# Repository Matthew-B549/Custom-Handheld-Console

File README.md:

# Custom-Handheld-Console
This repo is a collection of the hardware and software which make-up my Custom Handheld Console. You can find my PCB files here. I have also documented my thoughts and improvements that could be made to the project.

I have created a helpful pixel editor tool for creating artwork to display on the console. This tool can be found here: https://github.com/Matthew-B549/PixelEditor

**My inspiration**:
This project was largely inspired by the Nintendo Game Boy. In contrast to the cartridge style, all of the software is installed directly onto the ESP32. The software that I have uploaded includes 15 games (my favorite one being pong), but you are able to code in more of your own. The SD card (visible in the pictures at the bottom) is used to store high scores, but it can be repurposed in the software.

**Agentic Coding**:
In this project, I experimented with Agentic coding. I found that the various Agents that I used were able to iterate incredibly quickly to varying levels of results. Individually, many of the games are decently coded and perform well. However, I found that the Agents struggled in creating a unified system and some of the code is messy at times.

**What Changed V1 to V2?**
The primary change from V1 to V2 was in size. I shrunk the PCB from 133mm by 170mm to 100mm by 100mm. (*Note: I have no Idea how I chose the dimensions 133 by 170 originally, but the board went from being comically large to a more standard size*) This dramatic decrease in size led to more intentional routing being necessary. I completely remapped the ESP32 pins from V1 to V2 to optimize and reduce vias and crossing traces. I also focused on signal integrity by placing resistors along high frequency SPI communication lines. Additionally, I routed the speaker signal trace intentionally to try and minimize noise and crosstalk.

**What Changed V2 to V3?**
The only thing changed from V2 to V3 is the ESP32 footprint. In my first two versions, the PCB footprint was much smaller than my microcontroller's footprint. I had to bend the pins to make it fit in. This is mainly because of errors I made in measuring and using other models I had found online. To ensure that the V3 footprint is correct, I first made a CAD model of my ESP32 in Fusion. I then 3d printed it and made sure it was the exact same size. I then made the footprint with the same specifications from CAD and ensured that the CAD model and the footprint fit together.

**My Reflection**
This was my first project in which I made a PCB and I am exceptionally proud with the results. While there was much improvement from V1 to V2, there are still some issues I have come across when testing and using the Handheld Console. I have outlined some of the issues below:

* The ESP32 sometimes struggles to boot. This issue is likely due to weak battery connections and loosely attached power system on the back. On the back of the PCB, the battery, the buck boost converter, and the charging module are taped to the PCB. The PCB was not designed with this power system in mind. (In a similar fashion, the speaker is also taped to the back).

* I have not made a 3d printed case for this project. This is largely because of the irregular shape of the components mounted on the PCB. Large capacitors (among other components) poke through where the case would be. Again, the PCB was not designed specifically to work with a 3d printed case. These are all considerations that should be made earlier on in the process before ordering the PCB to ensure that both parts of the equation fit together.

* Even through my first 2 revisions and many measurements, the footprint for the ESP32 is slightly too small and pins may need to be bent in order to fit the footprint and be soldered in. ***This is fixed in V3***

* These design flaws heavily impact my experience when using the Console. They also make the Console very fragile and difficult to pass around and share.

I have included various pictures of the process and end result below.

Here is some of my earliest prototyping:
-----

Then I designed V1:
-----

V1 was way to big and had various flaws. Here is *a less flawed* V2:
-----

Notice the usage of tape:
-----

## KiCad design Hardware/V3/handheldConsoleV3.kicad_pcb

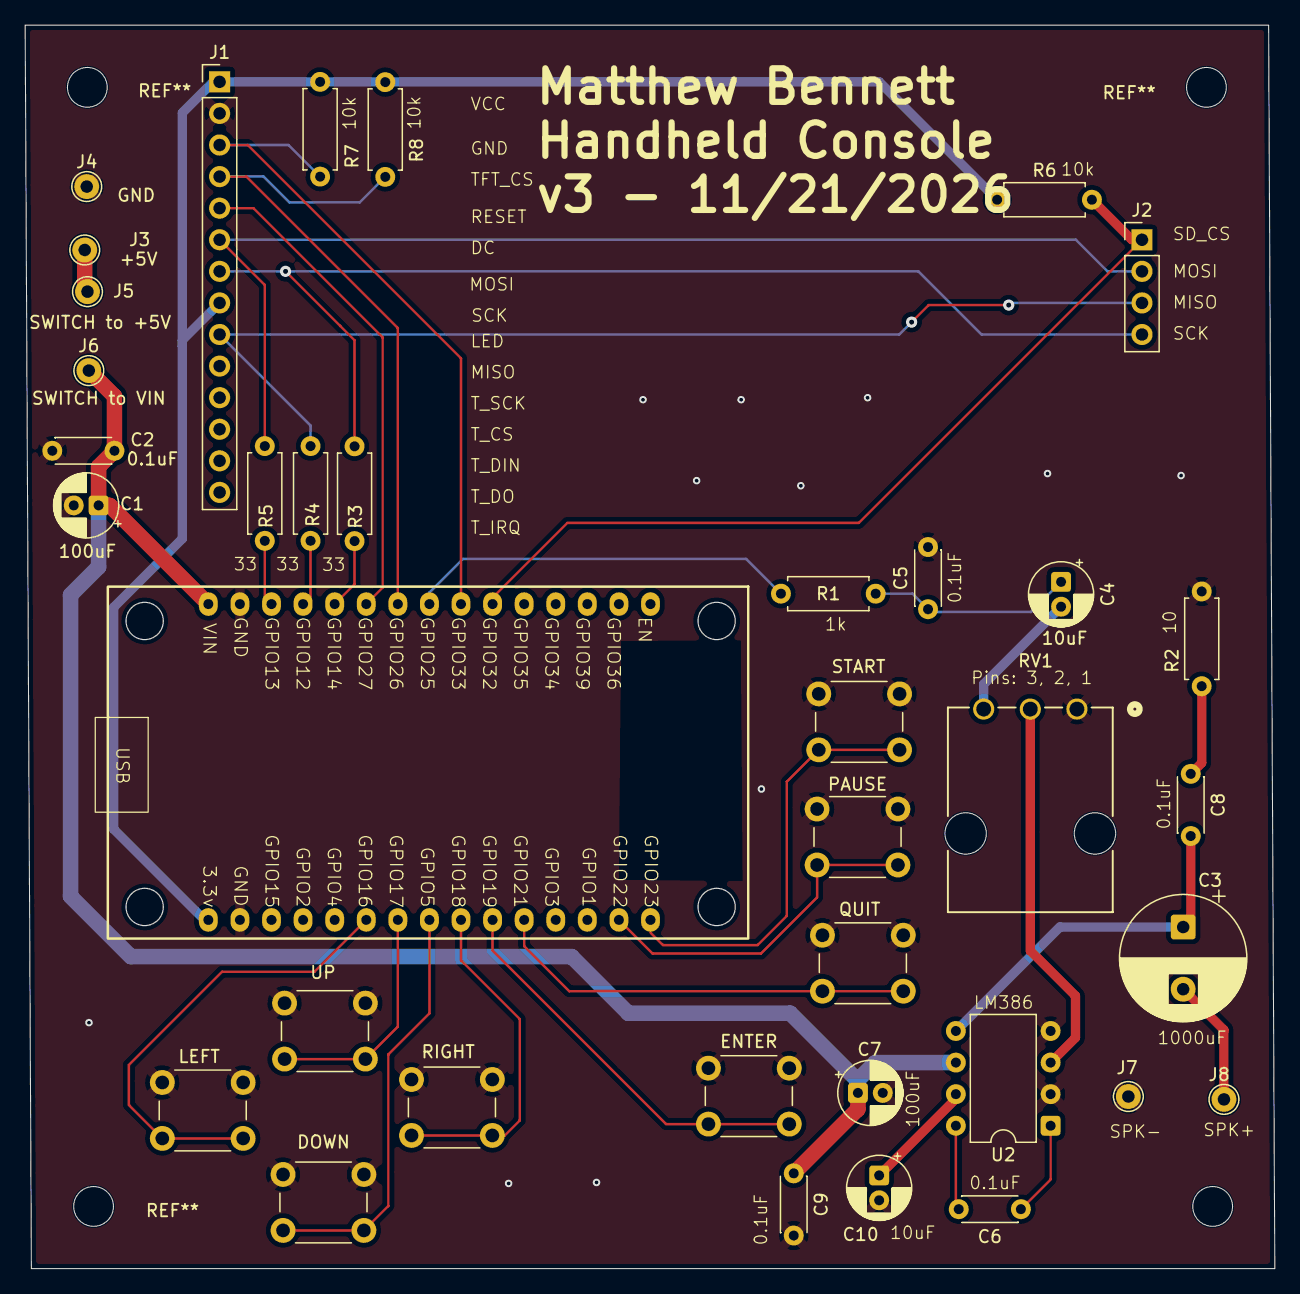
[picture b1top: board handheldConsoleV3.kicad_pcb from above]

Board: 2 copper layers, 100.5 x 100.0 mm, 37 parts (0 on the bottom side), 32 nets.

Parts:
C1, C7: 100uF; CP_Radial_D5.0mm_P2.00mm
C2, C5, C6, C8, C9: 0.1uF; C_Disc_D4.3mm_W1.9mm_P5.00mm
C3: 1000uF; CP_Radial_D10.0mm_P5.00mm
C4, C10: 10uF; CP_Radial_D5.0mm_P2.00mm
DOWN: SW_Push; SW_PUSH_6mm_H4.3mm
ENTER: SW_Push; SW_PUSH_6mm_H4.3mm
J1: Screen_Pins; PinHeader_1x14_P2.54mm_Vertical
J2: SD_Pins; PinHeader_1x04_P2.54mm_Vertical
J3, J4, J5, J6, J7, J8: Conn_01x01; TestPoint_THTPad_D2.0mm_Drill1.0mm
LEFT: SW_Push; SW_PUSH_6mm_H4.3mm
PAUSE: SW_Push; SW_PUSH_6mm_H4.3mm
QUIT: SW_Push; SW_PUSH_6mm_H4.3mm
R1: 1k; R_Axial_DIN0207_L6.3mm_D2.5mm_P7.62mm_Horizontal
R2: 10; R_Axial_DIN0207_L6.3mm_D2.5mm_P7.62mm_Horizontal
R3, R4, R5: 33; R_Axial_DIN0207_L6.3mm_D2.5mm_P7.62mm_Horizontal
R6, R7, R8: 10k; R_Axial_DIN0207_L6.3mm_D2.5mm_P7.62mm_Horizontal
RIGHT: SW_Push; SW_PUSH_6mm_H4.3mm
RV1: R_Potentiometer; POT_P120PK-x25_TTE
START: SW_Push; SW_PUSH_6mm_H4.3mm
U1: ESP32_30pin
U2: LM386; DIP-8_W7.62mm
UP: SW_Push; SW_PUSH_6mm_H4.3mm

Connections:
+3V3: J1.1, J1.8, R6.1, R7.1, R8.1, U1.16 (3.3v)
+5V: C1.1, C2.1, C7.1, C9.1, J6.1 (Pin_1_1), U1.1 (VIN), U2.6 (V+)
/DAC_AUDIO: R1.1, U1.8 (GPIO25)
/DC: J1.5, U1.6 (GPIO27)
/DOWN_BTN: DOWN.2, U1.23 (GPIO5)
/ENTER_BTN: ENTER.2, U1.25 (GPIO19)
/LEFT_BTN: LEFT.2, U1.21 (GPIO16)
/MISO: J1.9, J2.3, R4.2
/MOSI: J1.6, J2.2, R5.2
/PAUSE_BTN: START.2, U1.30 (GPIO23)
/QUIT_BTN: PAUSE.2, U1.29 (GPIO22)
/RESET: J1.4, R8.2, U1.7 (GPIO26)
/RIGHT_BTN: RIGHT.2, U1.24 (GPIO18)
/SCK: J1.7, J2.4, R3.2
/SD_CS: J2.1, R6.2, U1.10 (GPIO32)
/START_BTN: QUIT.2, U1.26 (GPIO21)
/TFT_CS: J1.3, R7.2, U1.9 (GPIO33)
/UP_BTN: U1.22 (GPIO17), UP.2
GND: C1.2, C2.2, C5.2, C7.2, C9.2, C10.2, DOWN.1, ENTER.1, J1.2, J4.1 (Pin_1_1), J7.1 (Pin_1_1), LEFT.1, PAUSE.1, QUIT.1, R2.1, RIGHT.1, RV1.1, START.1, U1.2 (GND), U1.17 (GND), U2.2 (-), U2.4 (GND), UP.1
unnamed: C3.1, C8.2, U2.5
unnamed: C4.1, C5.1, R1.2
unnamed: C4.2, RV1.3
unnamed: C6.1, U2.1 (GAIN)
unnamed: C6.2, U2.8 (GAIN)
unnamed: C8.1, R2.2
unnamed: J3.1 (Pin_1_1), J5.1 (Pin_1_1)
unnamed: C3.2, J8.1 (Pin_1_1)
unnamed: R4.1, U1.4 (GPIO12)
unnamed: R5.1, U1.3 (GPIO13)
unnamed: R3.1, U1.5 (GPIO14)
unnamed: RV1.2, U2.3 (+)
unnamed: C10.1, U2.7 (BYPASS)

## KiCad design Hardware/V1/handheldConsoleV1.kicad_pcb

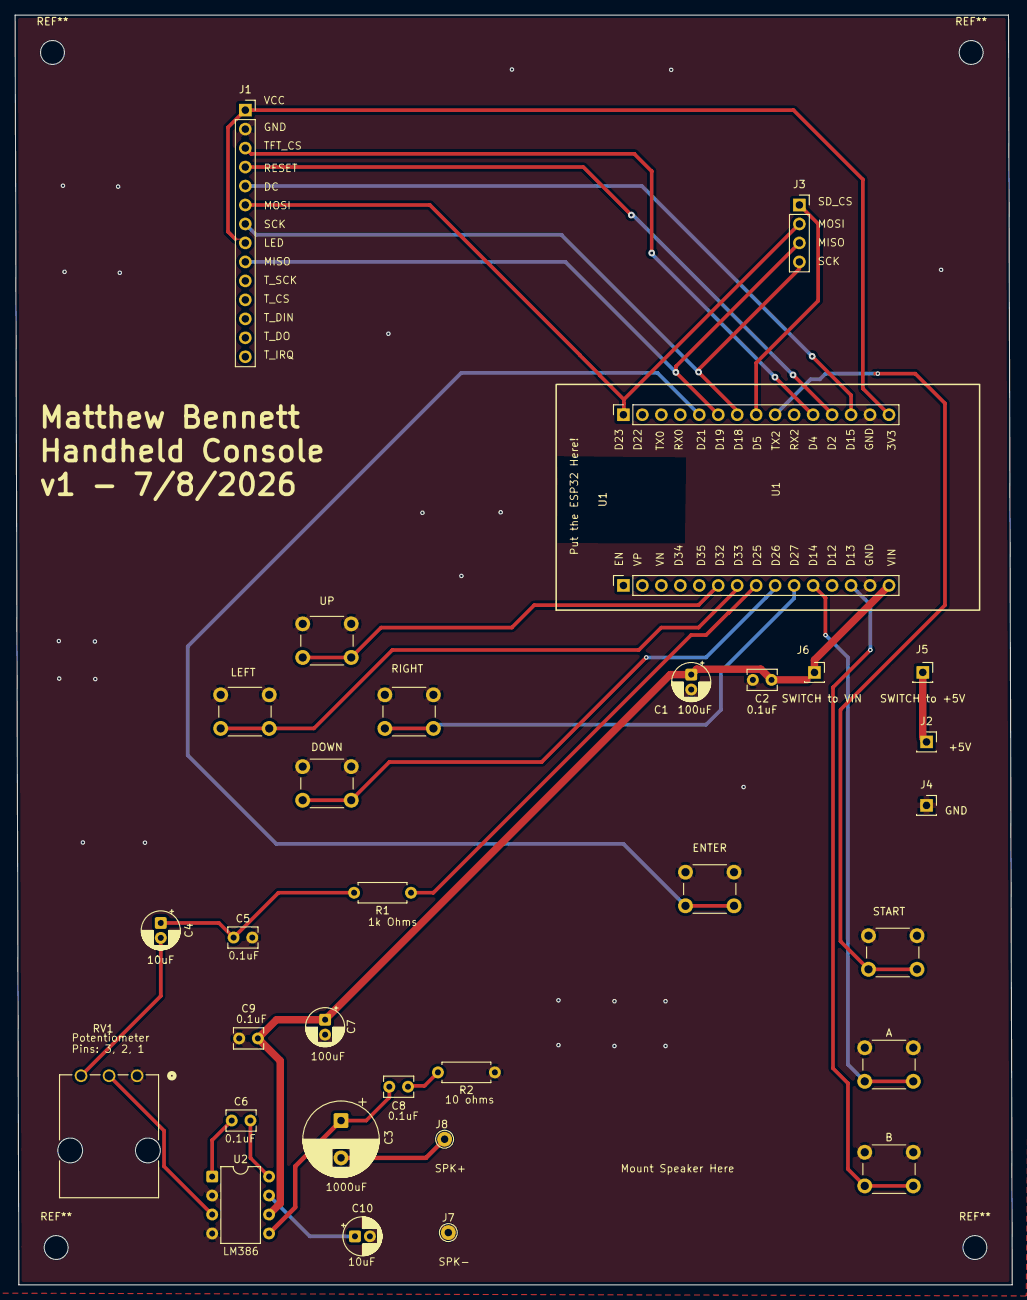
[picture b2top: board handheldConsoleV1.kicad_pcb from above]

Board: 2 copper layers, 133.5 x 170.0 mm, 31 parts (0 on the bottom side), 29 nets.

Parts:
A: SW_Push; SW_PUSH_6mm_H4.3mm
B: SW_Push; SW_PUSH_6mm_H4.3mm
C1, C7: 100uF; CP_Radial_D5.0mm_P2.00mm
C2, C5, C6, C8, C9: 0.1uF; C_Disc_D3.8mm_W2.6mm_P2.50mm
C3: 1000uF; CP_Radial_D10.0mm_P5.00mm
C4, C10: 10uF; CP_Radial_D5.0mm_P2.00mm
DOWN: SW_Push; SW_PUSH_6mm_H4.3mm
ENTER: SW_Push; SW_PUSH_6mm_H4.3mm
J1: Conn_01x14_Socket; PinSocket_1x14_P2.54mm_Vertical
J2, J4, J5, J6: Conn_01x01_Socket; PinSocket_1x01_P2.54mm_Vertical
J3: Conn_01x04_Socket; PinSocket_1x04_P2.54mm_Vertical
J7, J8: Conn_01x01; TestPoint_THTPad_D2.0mm_Drill1.0mm
LEFT: SW_Push; SW_PUSH_6mm_H4.3mm
R1: 1k; R_Axial_DIN0207_L6.3mm_D2.5mm_P7.62mm_Horizontal
R2: 10; R_Axial_DIN0207_L6.3mm_D2.5mm_P7.62mm_Horizontal
RIGHT: SW_Push; SW_PUSH_6mm_H4.3mm
RV1: R_Potentiometer; POT_P120PK-x25_TTE
START: SW_Push; SW_PUSH_6mm_H4.3mm
U1: SocketsForEsp32
U2: LM386; DIP-8_W7.62mm
UP: SW_Push; SW_PUSH_6mm_H4.3mm

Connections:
+3V3: J1.1, J1.8, U1.16 (3.3v)
+5V: C1.1, C2.1, C7.1, C9.1, J6.1 (Pin_1_1), U1.1 (VIN), U2.6 (V+)
GND: A.1, B.1, C1.2, C2.2, C5.2, C7.2, C9.2, C10.2, DOWN.1, ENTER.1, J1.2, J4.1 (Pin_1_1), J7.1 (Pin_1_1), LEFT.1, R2.1, RIGHT.1, RV1.1, START.1, U1.2 (GND), U1.17 (GND), U2.2 (-), U2.4 (GND), UP.1
unnamed: C3.1, C8.2, U2.5
unnamed: C4.1, C5.1, R1.2
unnamed: C4.2, RV1.3
unnamed: C6.1, U2.1 (GAIN)
unnamed: C6.2, U2.8 (GAIN)
unnamed: C8.1, R2.2
unnamed: J1.3, U1.20 (GPIO4)
unnamed: J1.4, U1.19 (GPIO2)
unnamed: J1.5, U1.18 (GPIO15)
unnamed: J1.6, J3.2, U1.30 (GPIO23)
unnamed: J1.7, J3.4, U1.24 (GPIO18)
unnamed: J1.9, J3.3, U1.25 (GPIO19)
unnamed: J2.1 (Pin_1_1), J5.1 (Pin_1_1)
unnamed: J3.1, U1.23 (GPIO5)
unnamed: C3.2, J8.1 (Pin_1_1)
unnamed: B.2, U1.3 (GPIO13)
unnamed: A.2, U1.5 (GPIO14)
unnamed: START.2, U1.22 (GPIO17)
unnamed: ENTER.2, U1.26 (GPIO21)
unnamed: R1.1, U1.8 (GPIO25)
unnamed: DOWN.2, U1.7 (GPIO26)
unnamed: RIGHT.2, U1.6 (GPIO27)
unnamed: U1.10 (GPIO32), UP.2
unnamed: LEFT.2, U1.9 (GPIO33)
unnamed: RV1.2, U2.3 (+)
unnamed: C10.1, U2.7 (BYPASS)
